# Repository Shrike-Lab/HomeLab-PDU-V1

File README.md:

<div align="center">

  [Website](https://www.shrikelab.co) | [YouTube](https://www.youtube.com/@ShrikeLab)
  
</div>
<p align="center">

</p>

# **ShrikeLab PDU V1** - 5 & 10 port USB-C PDUs for 10" and 19" racks
These PSUs are power delivery solutions for micro PC clusters and homelabs that suits either 10" and 19" racks. All variants are built around a Meanwell HRP-300-24 featuring either 5 or 10 USB-C power delivery ports enclosed in sheet metal or 3D printed ABS/ASA housings. 

<div align="center">
  <a
    href="https://www.Shrikelab.co" title="Kits and PCBs available now!">Kits and PCBs available now!
  </a>  
</div>

---

Mini and micro labs are a great solution for homelabbing, but the power delivery options are often bulky and hard to manage due to the need for an individual power brick per computer.
This project helps fix this by consolidating power delivery for up to 10 65W micro PCs into a single unit that fits in either a 10" or 19" 1U rack. This differs from a conventional multi-port USB PD hub by not needing to re-negotiate any power delivery voltages when a unit is turned off or unplugged, or when the power load across ports changes drastically. Also the packaging is designed specifially for rack mounting, with active cooling and simple power switching.

[**Design and build video here**](https://www.youtube.com/watch?v=8tTG0TBM7ts)

[**Follow-up and testing video here**](https://www.youtube.com/watch?v=Ig7oZpujHtc&t)

<br>

### Features:
- Imperial sheet metal compatible for the 10in single variant!
- Both 19" and 10" variants
- Up to 10 x 65W USB-C outputs
- 1U Height
- Active cooling
- Sheet metal housing or fully 3D printable
- All variants built around a Meanwell HRP-300-24
- All 3D printed parts fit on a 220x220mm print bed

<br>

### Repo Content:
- **Assembly** - Renders and references for main and sub-assemblies, plus bill of material for each variant
  - **CAD** - CAD files for all varients, universal files and drawings of components
    - **Universal** - Files thats are used for multiple variants
    - 10in_Single
    - 10in_Single_Imperial - edited for .048" (1.2mm) sheet metal, SendCutSend compatible
    - 10in_Dual
    - 10in_3D_Modular
    - 10in_3D_Unibody
    - 19in_Single
    - 19in_Dual
    - 19in_Dual_SBS
    - **Blanks** - STP files for customisation
    - **Universal** - STL and STP files that are used for multiple variants
  - **Drawings** - Drawings of components and wiring
    - **Electrical** - Harness pinouts and drawings of electronic components
    -  **Hardware** - Drawings of hardware along with sheet metal engineering drawings
- **IMG** - Images
- **PCB** - PCB gerber manufacturing files

<br>

### Issues:
There's a lot of ground to cover with this repo, so if you find an issue, please raise it with the GitHub issue system and it will get fixed. If you have questions about assembly or any of the variants, please make sure you have read through all the readme content before reaching out to save on time.

### ToDo:
- Export all sheet metal STEP files in 1.2mm thickness for imperial

# Variants:
All variants are built around a Meanwell HRP-300-24 and the same PCB. The housings are designed to fit in 1U of space in either a 10in and 19in server rack. 

## 10 Inch - Single:
The original 10" enclosure, a sheet metal body + lid make up the housing, with a 3D printed front and rear. 5 outputs.

[Bill of materials](https://github.com/Shrike-Lab/MiniLab-PSU/blob/main/ASSEMBLY/README.md#10-inch---single)

<br>

## 10 Inch - 3D Printed - Unibody:
10" printed unibody enclosure, made to be as easy as possible with minimal additional hardware, with the trade-off of being a little harder to print. No inserts required, all bolts thread directly into the print material. Small hatch for attaching button + fan and connecting wiring to PCB.

[Bill of materials](https://github.com/Shrike-Lab/MiniLab-PSU/blob/main/ASSEMBLY/README.md#10-inch---3d-printed---unibody)

<br>

## 10 Inch - 3D Printed - Modular:
10" printed enclosure, made to be more modular and mod-friendly but requires more M3 inserts and bolts to assebmle. The CAD folder for this variant also includes 'flipped' front and rear STLs that have the mounting tabs swapped, so that the USB-C ports and power intput will face the front of the rack instead of the rear.

[Bill of materials](https://github.com/Shrike-Lab/MiniLab-PSU/blob/main/ASSEMBLY/README.md#10-inch---3d-printed---modular)

<br>

## 10 Inch - Dual:
10" enclosure for external PSU's. 10 outputs, intended for use with alternative power sources like battery or solar, or for up-cycling external 300W PSUs.

[Bill of materials](https://github.com/Shrike-Lab/MiniLab-PSU/blob/main/ASSEMBLY/README.md#10-inch---dual)

<br>

## 19 Inch - Single:
19" inch version of 5 output variant. Additional space could be used for cable / tiny-mini-micro storage.

[Bill of materials](https://github.com/Shrike-Lab/MiniLab-PSU/blob/main/ASSEMBLY/README.md#19-inch---single)

<br>

## 19 Inch - Dual:
19" with 10 outputs from 2 x internal assemblies.

[Bill of materials](https://github.com/Shrike-Lab/MiniLab-PSU/blob/main/ASSEMBLY/README.md#19-inch---dual)

<br>

## 19 Inch - SBS:
For people that couldn't possibly deal with a power input in the middle of the housing, this version has matching components side-by-side so inputs and outputs can be coordinated easier. One harness will require extending due to the layout.

[Bill of materials](https://github.com/Shrike-Lab/MiniLab-PSU/blob/main/ASSEMBLY/README.md#19-inch---dual---sbs)

<br>

# Disclaimer:

If you build, modify, or use this project, you do so entirely at your own risk. The author provides these files without any warranty or guarantee of safety, reliability, or fitness for any particular purpose, and accepts no liability for any damage, injury, loss, or other consequences resulting from their use.

# License:
This project is licensed under the CERN Open Hardware Licence Version 2 - Strongly Reciprocal (CERN-OHL-S v2).
You may use, study, modify, and distribute this design and its documentation, provided that any derivatives are licensed under the same terms. Source design files must be made available to anyone who receives the hardware or design files.

Learn more about the license at [ohwr.org](https://ohwr.org).

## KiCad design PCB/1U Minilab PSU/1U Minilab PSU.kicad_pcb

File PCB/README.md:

# PCB:
All variants use the same 2 layer 1.6mm thick PCB. This folder contains production files that can be uploaded to a PCB service for manufacturing, JLCPCB is my go-to. PCB assembly is recommended unless you have capability to do SMD soldering with either a hot air station or reflow oven.
There is currently no option for a through-hole variant because the tranistor does not come in a TH package.

**Parameters for PCB manufacturing:**
- 2 Oz copper trace weight - This is a must for current rating
- 1.6mm PCB thickness

<br>

### PCB Notes:
- You can use either an LM2596S or and MP1584EN. Just move the mounting headers to the corresponding holes.
- Connectors J19, J20, J21, J22 are optional. Either used for additional power output, or testing.
- After assembly, set fan header output voltage **before** plugging any fans in.

<br>

### Power Delivery Modules:
THe board assembly contains 5 USB-C power delivery modules that are based on an XPM52C with the following power profiles.

12V/3A, 15V/3A, 20V/3.25A

**Low Power PDO:** 5V/3A, 9V/3A, 12V/2.5A, 20V/1.5A

**High Power PDO:** 5V/3A, 9V/3A, 12V/3A

There's an interesting article [here](https://mysku.club/blog/aliexpress/101076.html) (is in Russian so will need translating) that goes over the thermal performance of the power delivery chips at 65W.

### Buck Converter:
To power the 40mm chassis fans the main 24V rail needs to be stepped down to 12V. This can be done with either an LM2596S or MP1584EN, on the PCB there's header holes and labels for both. The LM2596S is much more popular, but the MP1584EN is newer and has less EMC. MP1584EN comes in multiple variants, **make sure to get the variable one so you're able to tune the fan voltage**.

### Cooling Fan:
The cooling fan used for the PCB is a Noctua NF-A4x20 powered via 12V stepped down from the switched 24V output. This fan is 40mmx40mm and 20mm thick. The fan output on the main PCB is DC only, so the 3-Pin FLX variant are recommended, however the 4-pin PWM version will also work. When assembling the main PCB, make sure to adjust the buck converter output voltage down below 12V before plugging in any fans. The RPM of the fans is adjusted by tuning the voltage output of the buck converter.

Replacing the internal fan of the Meanwell PSU requires opening the power supply unit. This should only be attempted by qualified personnel.
Mains voltage is present inside the PSU enclosure and can cause serious injury or death. Even with the unit powered off and unplugged, capacitors inside the PSU may retain a lethal charge for an extended period. Do not touch any internal components unless you are certain the unit has been fully discharged.

If you chose to replace the PSU fan, it can be plugged into the second header on the main PCB.

The fan headers on the PCB are 3 pin 2.54mm, standard DC fan headers.

### Wiring:
There are two harnesses per set of internal electronics, one for main power and one for the button. The drawings can be found [here](https://github.com/Shrike-Lab/MiniLab-PSU/tree/main/ASSEMBLY/DRAWINGS/Electrial).

- **I would highly recommend you double check the pinout of your latching button before wiring it up, as they can differ from brand to brand.**

| Part          | Harness            | Quantity Per Assembly | Link                                                                                                     |
| ------------- | ------------------ | --------------------- | -------------------------------------------------------------------------------------------------------- |
| Ring spade    | 24V Power          | 9                     | https://www.digikey.com/en/products/detail/molex/0193240008/3884473                                      |
| PCB Connector | 24V Power & Button | 2                     | https://www.digikey.com/en/products/detail/molex/0039012060/61379?s=N4IgTCBcDaIOoFkDMB2ADGAtAOQCIgF0BfIA |
| Crimp         | 24V Power & Button | 12                    | https://www.digikey.com/en/products/detail/molex/0039000039/61448?s=N4IgTCBcDaIOoFkwFYAMBGAtAOQCIgF0BfIA |
| IEC Terminals | Mains Power        | 7                     | https://www.digikey.com/en/products/detail/molex/0190030011/279039                                       |

<br>

## PCB Component BOM:

| Type      | Key                  | Value     | Footprint         | Quantity | Component       | Commment         |
| --------- | -------------------- | --------- | ----------------- | -------- | --------------- | ---------------- |
| Capacitor | C1,C2,C5,C6,C7,C8,C9 | 470uF     | THT-CP_Radial_D10 | 6        | -               | -                |
| Capacitor | C3                   | 1uF       | 1206              | 1        | -               | -                |
| Capacitor | C4                   | 220nF     | 0603              | 1        | -               | -                |
| Capacitor | C10,C11,C12,C13,C14  | 1uF       | 1206              | 5        | -               | -                |
| Capacitor | C15,C16,C17,C18,C19  | .1uF      | 0603              | 5        | -               | -                |
| Resistor  | R1                   | 4.7k      | 1206              | 1        | -               | -                |
| Resistor  | R2                   | 47k       | 0603              | 1        | -               | -                |
| Resistor  | R3                   | 100       | 0603              | 1        | -               | -                |
| Resistor  | R4                   | 100k      | 0603              | 1        | -               | -                |
| Diode     | D1,D2,D3,D4,D5       | SMBJ26A   | D_SMB             | 5        | -               | -                |
| Diode     | D6                   | SMCJ26A   | D_SMC             | 1        | -               | -                |
| Diode     | D7                   |     Zener | SOD-123           | 1        | BZT52C12        | -                |
| Fuse      | F1                   | 15A       | 2410              | 1        | 0451020.MRL     | -                |
| Fuse      | F2,F3,F4F5,F6        | 3A        | 1206              | 5        | 1206FA-4A       | -                |
| Connector | J1,J2                | -         | Molex_5569-06A2   | 2        | Molex_5569-06A2 | Power and button |
| Connector | J13,J14,J15,J16      | -         | 1x01_2.54mm       | 4        | 1x01_2.54mm     | Buck converter   |
| Connector | J17,J18              | -         | Molex_2272031     | 2        | Molex_2272031   | Fans             |
| Connector | J19,J21,J22          | -         | 1x02_2.54mm       | 3        | 1x02_2.54mm     | Debug            |
| Connector | J20                  | -         | JST_PH-K_1x02     | 1        | JST_PH-K_1x02   | PSU sense        |
| Mosfet    | Q1                   | -         | TO-263-2L         | 1        | NCEP40PT15D     | -                |

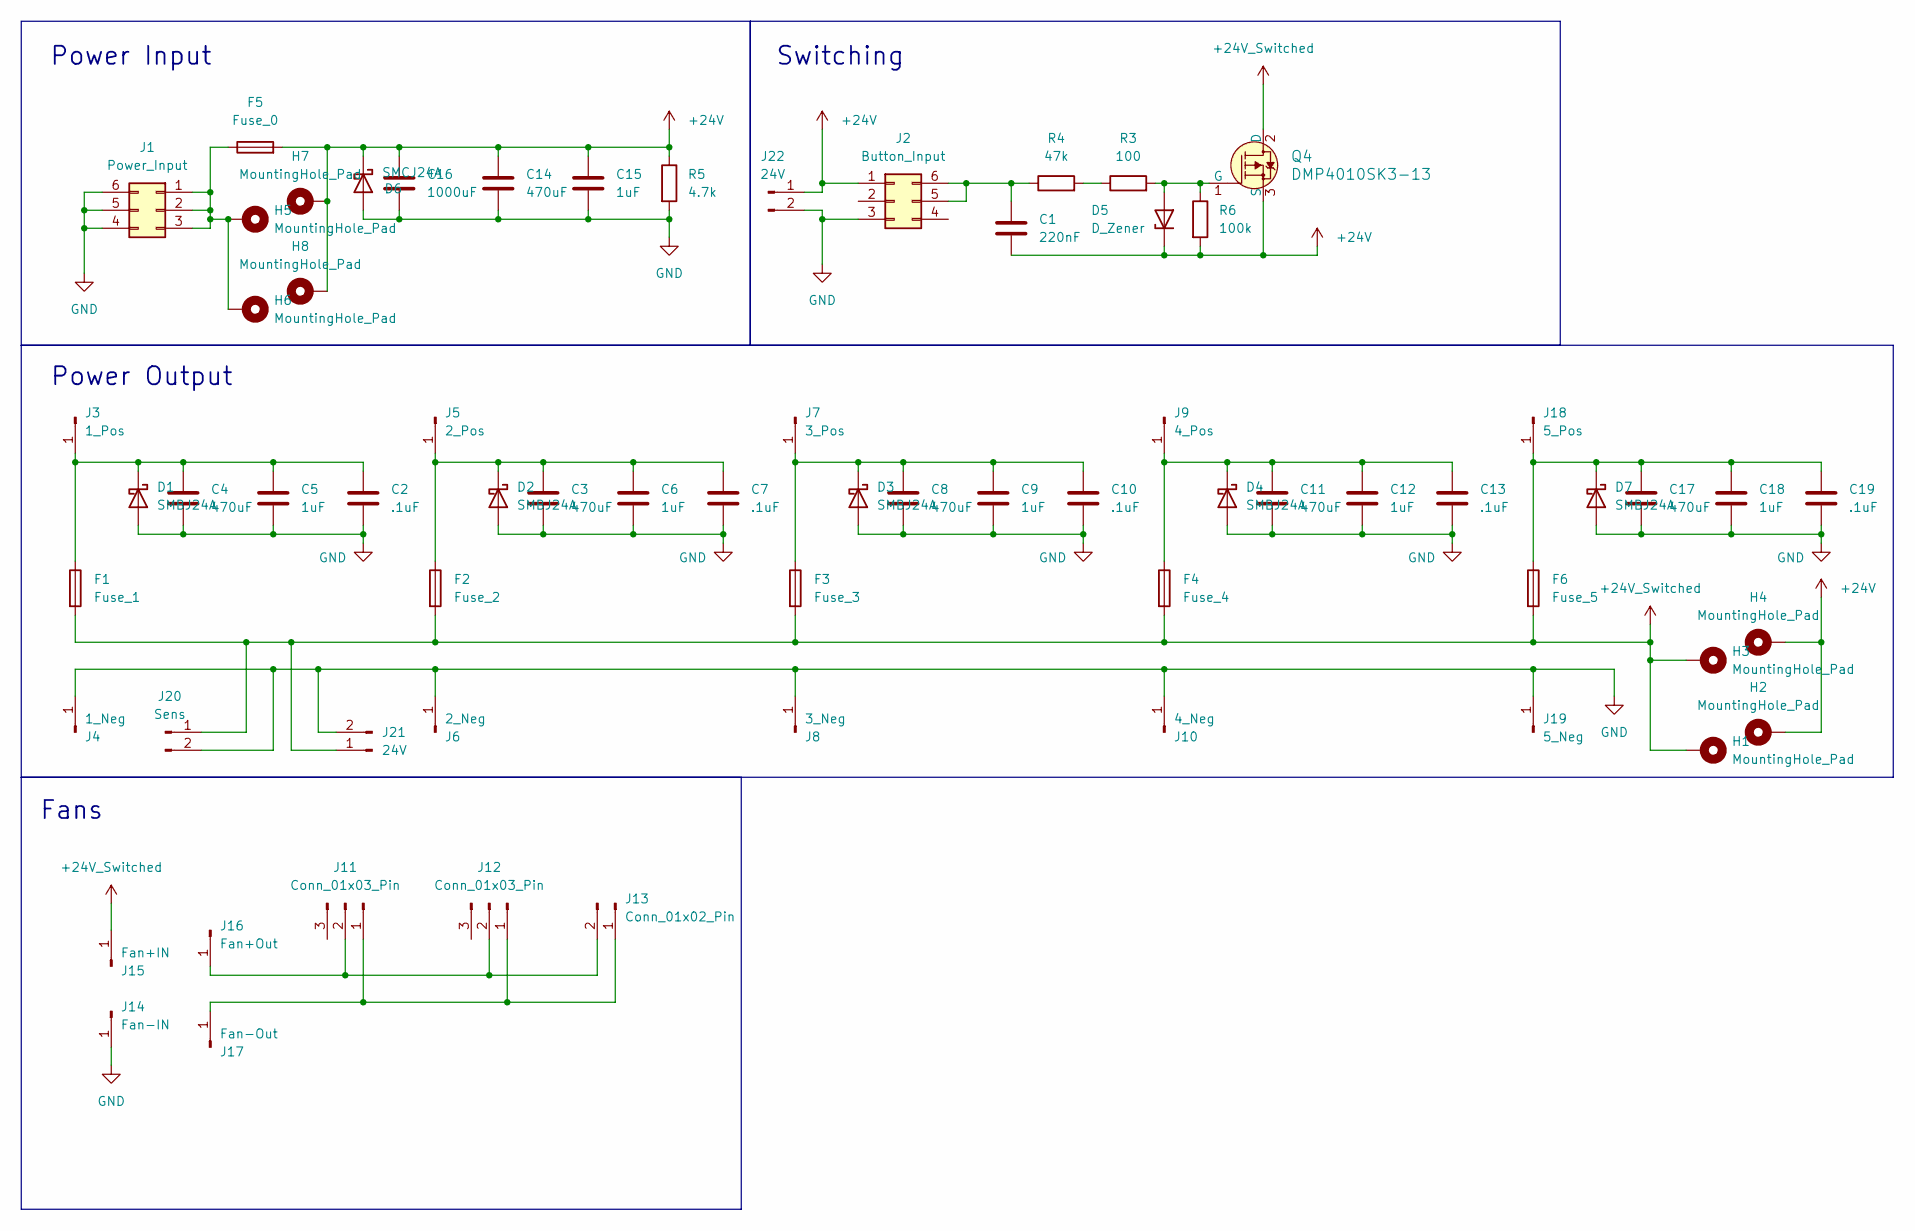
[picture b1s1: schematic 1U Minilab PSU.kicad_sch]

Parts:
C1: 220nF; C_0603_1608Metric_Pad1.08x0.95mm_HandSolder
C2, C7, C10, C13, C19: .1uF; C_0603_1608Metric_Pad1.08x0.95mm_HandSolder
C3, C4, C8, C11, C14, C17: 470uF; CP_Radial_D10.0mm_P5.00mm
C5, C6, C9, C12, C15, C18: 1uF; C_1206_3216Metric_Pad1.33x1.80mm_HandSolder
C16: 1000uF; CP_Radial_D10.0mm_P5.00mm
D1, D2, D3, D4, D7: SMBJ24A; D_SMB
D5: D_Zener; D_SOD-123
D6: SMCJ24A; D_SMB-SMC_Universal_Handsoldering
F1: Fuse_1; Fuse_1206_3216Metric_Pad1.42x1.75mm_HandSolder
F2: Fuse_2; Fuse_1206_3216Metric_Pad1.42x1.75mm_HandSolder
F3: Fuse_3; Fuse_1206_3216Metric_Pad1.42x1.75mm_HandSolder
F4: Fuse_4; Fuse_1206_3216Metric_Pad1.42x1.75mm_HandSolder
F5: Fuse_0; Fuse_1206_3216Metric_Pad1.42x1.75mm_HandSolder
F6: Fuse_5; Fuse_1206_3216Metric_Pad1.42x1.75mm_HandSolder
H1, H2, H3, H4, H5, H6, H7, H8: MountingHole_Pad; MountingHole_2.2mm_M2_DIN965_Pad_TopBottom
J1: Power_Input; Molex_Micro-Fit_3.0_43045-0600_2x03_P3.00mm_Horizontal
J2: Button_Input; Molex_Micro-Fit_3.0_43045-0600_2x03_P3.00mm_Horizontal
J3: 1_Pos; PinHeader_1x01_P2.54mm_Vertical
J4: 1_Neg; PinHeader_1x01_P2.54mm_Vertical
J5: 2_Pos; PinHeader_1x01_P2.54mm_Vertical
J6: 2_Neg; PinHeader_1x01_P2.54mm_Vertical
J7: 3_Pos; PinHeader_1x01_P2.54mm_Vertical
J8: 3_Neg; PinHeader_1x01_P2.54mm_Vertical
J9: 4_Pos; PinHeader_1x01_P2.54mm_Vertical
J10: 4_Neg; PinHeader_1x01_P2.54mm_Vertical
J11, J12: Conn_01x03_Pin; PinHeader_1x03_P2.54mm_Vertical
J13: Conn_01x02_Pin; PinHeader_1x02_P2.54mm_Vertical
J14: Fan-IN; PinHeader_1x01_P2.54mm_Vertical
J15: Fan+IN; PinHeader_1x01_P2.54mm_Vertical
J16: Fan+Out; PinHeader_1x01_P2.54mm_Vertical
J17: Fan-Out; PinHeader_1x01_P2.54mm_Vertical
J18: 5_Pos; PinHeader_1x01_P2.54mm_Vertical
J19: 5_Neg; PinHeader_1x01_P2.54mm_Vertical
J20: Sens; PinHeader_1x02_P2.54mm_Vertical
J21, J22: 24V; PinHeader_1x02_P2.54mm_Vertical
Q4: DMP4010SK3-13; TO-252-3_TabPin2; MPN IRF9540NPBF; Digi-Key_PN IRF9540NPBF-ND
R3: 100; R_0603_1608Metric
R4: 47k; R_0603_1608Metric
R5: 4.7k; R_1206_3216Metric
R6: 100k; R_0603_1608Metric

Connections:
+24V: C1.2, C14.1, C15.1, C16.1, D5.1 (K), D6.1 (K), F5.2, H2.1, H4.1, H7.1, H8.1, J2.1, J22.1, Q4.3 (S), R5.1, R6.2
+24V_Switched: F1.2, F2.2, F3.2, F4.2, F6.2, H1.1, H3.1, J15.1, J20.1, J21.1, Q4.2 (D)
GND: C2.2, C3.2, C4.2, C5.2, C6.2, C7.2, C8.2, C9.2, C10.2, C11.2, C12.2, C13.2, C14.2, C15.2, C16.2, C17.2, C18.2, C19.2, D1.2 (A), D2.2 (A), D3.2 (A), D4.2 (A), D6.2 (A), D7.2 (A), J1.4, J1.5, J1.6, J2.3, J4.1, J6.1, J8.1, J10.1, J14.1, J19.1, J20.2, J21.2, J22.2, R5.2
unnamed: C2.1, C4.1, C5.1, D1.1 (K), F1.1, J3.1
unnamed: C3.1, C6.1, C7.1, D2.1 (K), F2.1, J5.1
unnamed: C8.1, C9.1, C10.1, D3.1 (K), F3.1, J7.1
unnamed: C11.1, C12.1, C13.1, D4.1 (K), F4.1, J9.1
unnamed: D5.2 (A), Q4.1 (G), R3.2, R6.1
unnamed: C17.1, C18.1, C19.1, D7.1 (K), F6.1, J18.1
unnamed: F5.1, H5.1, H6.1, J1.1, J1.2, J1.3
unnamed: C1.1, J2.5, J2.6, R4.1
unnamed: J11.1, J12.1, J13.1, J17.1
unnamed: J11.2, J12.2, J13.2, J16.1
unnamed: R3.1, R4.2

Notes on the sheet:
Fans
Power Output
Power Input
Switching

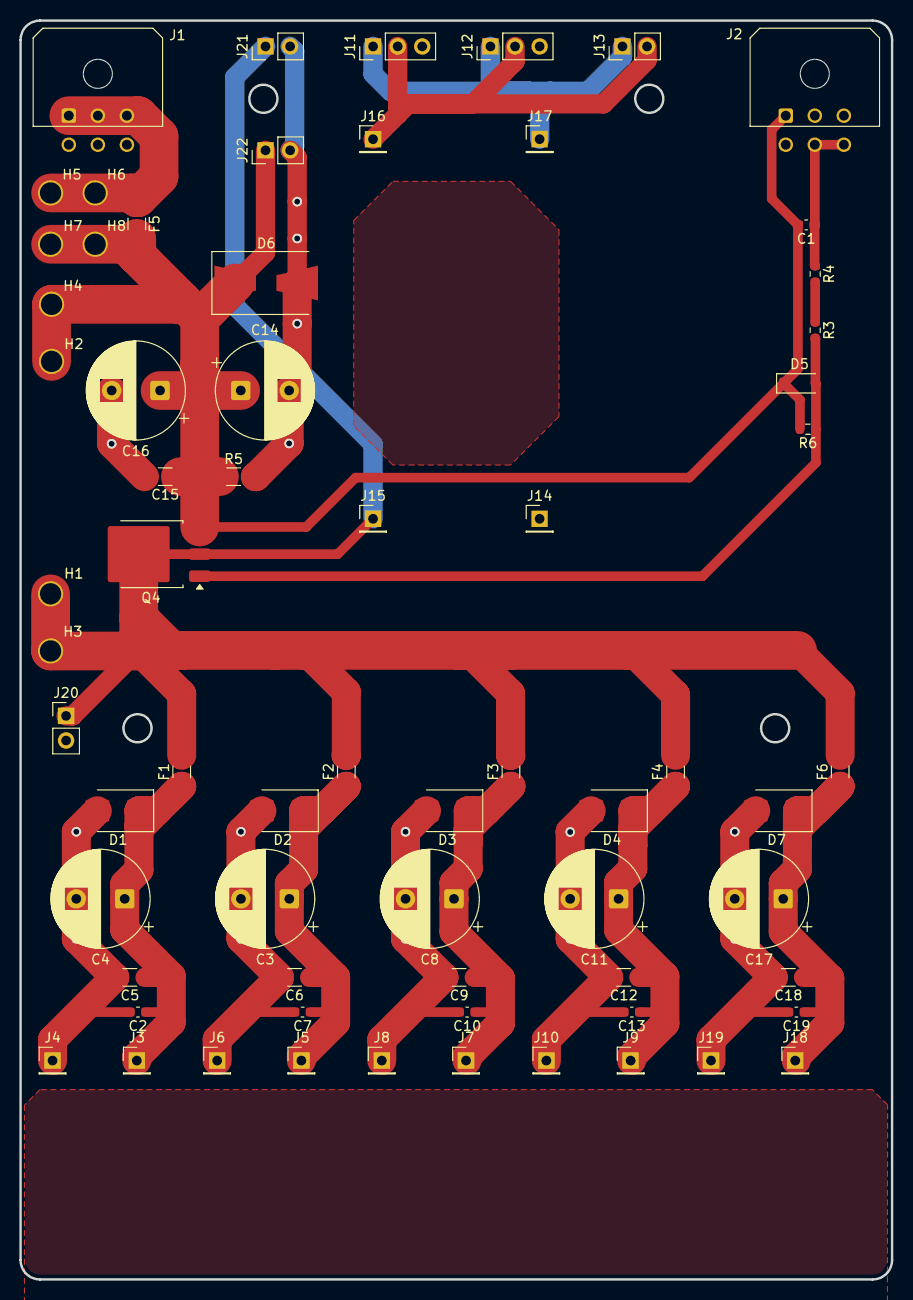
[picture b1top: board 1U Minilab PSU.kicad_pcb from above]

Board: 2 copper layers, 90.0 x 130.0 mm, 67 parts (0 on the bottom side), 14 nets.

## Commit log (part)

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2025-12-24 Pushing KiCad files
2025-12-27 changing footprint of mosfet
2026-02-23 Working on README
2026-02-23 Added front images
2026-02-23 Links to stls
2026-02-23 added render
2026-03-15 header
2026-03-15 insert drawing
2026-03-15 readme updates
2026-03-15 Rename BOM.md to README.md
2026-03-16 readme update
2026-03-16 real img
2026-03-17 updating
2026-03-26 Added schematics
2026-03-28 folders
2026-03-29 structure
2026-03-31 changes to PCB
2026-03-31 updated pcb
2026-03-31 links broken
2026-04-01 added blanks
2026-04-04 JLC and PCBWay exports
2026-04-04 Rename Reinforcement_Bracket.STL to Reinforcement_Bracket.stl
2026-04-05 Fixed 19in single rear and added blank STEP
2026-06-16 Added OBD++ .tgz
